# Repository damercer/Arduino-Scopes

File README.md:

# Arduino firmware for Universal-ALICE
With the goal of "Instrumentation for Every Student" in mind this project is intended to lower all barriers to providing a hardware and software platform for teaching electronic circuits to engineering students. Every student should have access to affordable hardware and software to measure their experiments.
This project offers a free open source software user interface that is compatible with hardware produced in large quantities at low cost (ranging from $5 to $20) from multiple suppliers.
#
Currently available hardware interfaces (some are works in progress):

* Arduino compatible microcontroler boards:
  + Adafruit QT Pi - SAMD21
  + Adafruit Trinket M0 (ATSAMD21)
  + Adafruit ItsyBitsy M0 Express (ATSAMD21)
  + Adafruit ItsyBitsy M4 Express (ATSAMD51)
  + Raspberry Pi Pico RP-2040
    - With external R/2R DAC or SPI DAC or PWM analog AWG output
  + SparkFun SAMD21 Mini Breakout (DEV-13664)
  + SparkFun Thing Plus - SAMD51 (DEV-14713)
  + Seeed Studio XIAO SAMD21
  + Seeed Studio XIAO RP-2040
    - With external SPI DAC or PWM analog AWG output

If you are not a technical individual or highly familiar with computer operating systems and you have your choice of computers, a Windows computer is highly recommended. You will usually run into fewer issues, if any, with that operating system.

Known Issues: If your computer encrypts files saved on external storge devices (USB disk drives) then the UF2 Bootloader method of flashing firmware to micro-controller boards will not work. You would need to use a different computer that does not encrypt files or consult your local system administrator.

Linux Operating system: On Linux computers access to USB based serial comms devices is not allowed for non root users by default. A udev rules file needs to be added. Place the 99-arduino.rules from this repository in etc/udev/rules.d

It contains one line per board / vendor:

SUBSYSTEMS=="usb", ATTRS{idVendor}=="802F", ATTRS{idProduct}=="2886", GROUP="dialout", MODE="0666"

The above idVendor value is board / vendor specific and may need to be adjusted to match your specific board(s). The one above is specifically for the XIAO SAMD21 board.

If this rules file does not work on your version of Linux there may be other things like this that work. Searching the web on how to make serial USB devices work may provide an alternate solution or consult with your local Linux expert.

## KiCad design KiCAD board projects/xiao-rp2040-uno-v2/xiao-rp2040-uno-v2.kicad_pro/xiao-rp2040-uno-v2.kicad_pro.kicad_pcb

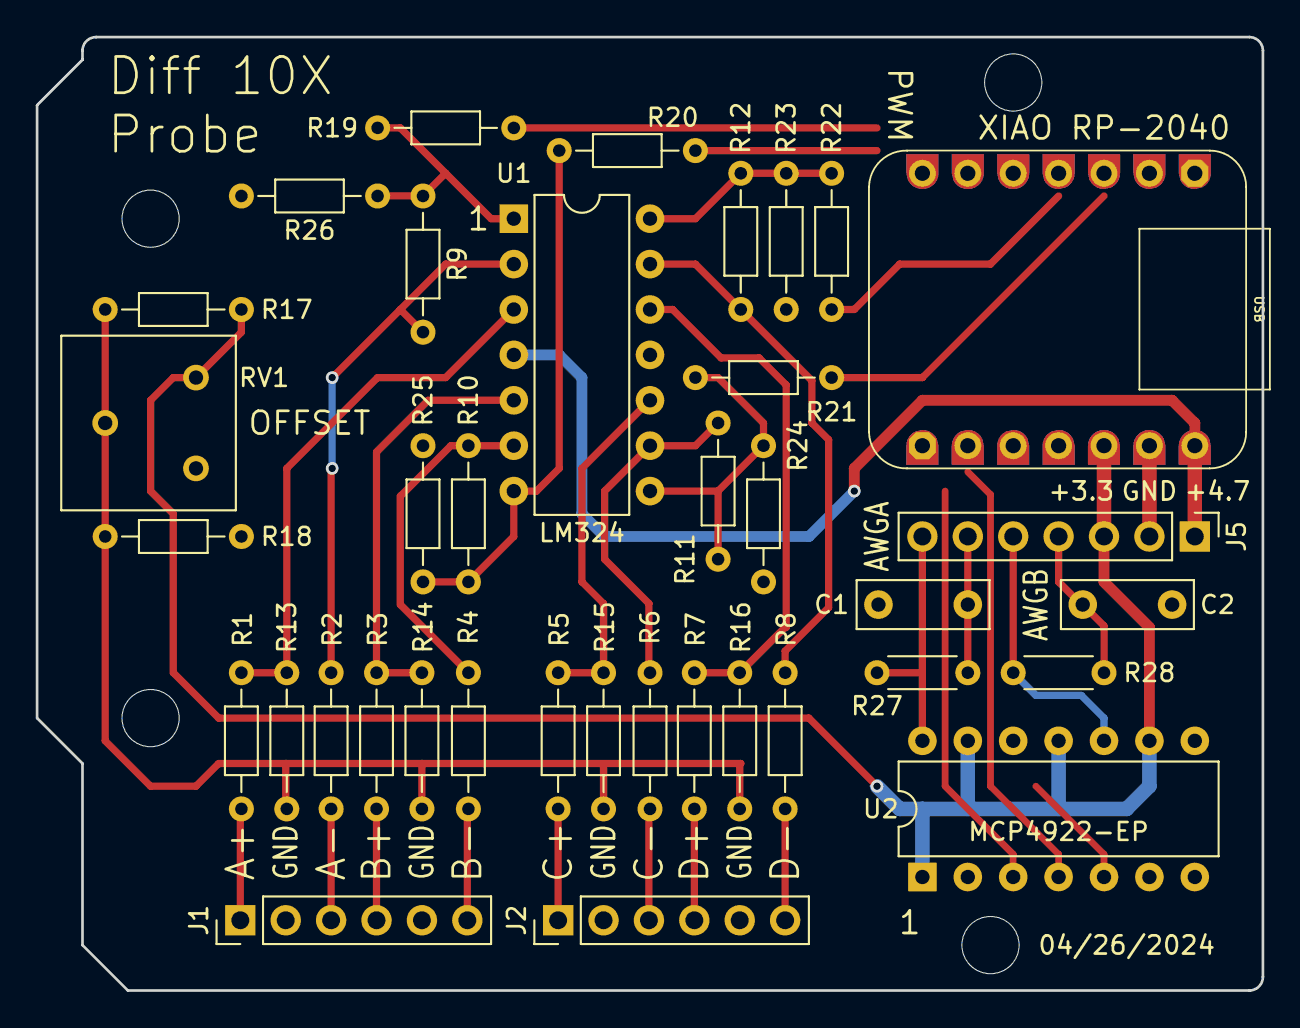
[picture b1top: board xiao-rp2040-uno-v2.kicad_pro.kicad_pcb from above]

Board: 6 copper layers, 68.6 x 53.3 mm, 42 parts (0 on the bottom side), 35 nets.

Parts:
C1, C2: C; C_Rect_L7.2mm_W2.5mm_P5.00mm_FKS2_FKP2_MKS2_MKP2
J1, J2: Conn_01x06_Pin; PinHeader_1x06_P2.54mm_Vertical
J2#2, J4: DNP; H7-HALF-HOLE-2.54
J5: Conn_01x07_Pin; PinHeader_1x07_P2.54mm_Vertical
MH1, MH2, MH3, MH4: MountingHole_3.2mm
R1, R2, R3, R4, R5, R6, R7, R8: 1Meg; R_Axial_DIN0204_L3.6mm_D1.6mm_P7.62mm_Horizontal
R9, R10, R11, R12, R13, R14, R15, R16: 100k; R_Axial_DIN0204_L3.6mm_D1.6mm_P7.62mm_Horizontal
R17, R18: 100; R_Axial_DIN0204_L3.6mm_D1.6mm_P7.62mm_Horizontal
R19, R20, R21, R22: 220; R_Axial_DIN0204_L3.6mm_D1.6mm_P7.62mm_Horizontal
R23, R24, R25, R26: 510; R_Axial_DIN0204_L3.6mm_D1.6mm_P7.62mm_Horizontal
R27, R28: 1k; R_Axial_DIN0204_L3.6mm_D1.6mm_P5.08mm_Horizontal
RV1: 500; Potentiometer_Bourns_3386F_Vertical
U1: LM324; DIP-14_W7.62mm
U2: MCP4922-EP; DIP-14_W7.62mm

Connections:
3V3: J4.5, J5.3, R17.1, RV1.1, U2.1 (VDD), U2.9 (~SHDN), U2.11 (VrefB), U2.13 (VrefA)
A0: J2#2.1, R19.1
A1: J2#2.2, R20.1
A2: J2#2.3, R21.1
A3: J2#2.4, R22.1
GND: C1.2, C2.2, J1.2, J1.5, J2.2, J2.5, J4.6, J5.2, R18.2, R23.2, R24.2, R25.2, R26.2, RV1.3, U1.11 (V-), U2.8 (~LDAC), U2.12 (AVSS)
MOSI: J4.4, U2.5 (SDI)
unnamed: J1.1, R1.2
unnamed: J1.3, R2.2
unnamed: J1.4, R3.2
unnamed: J1.6, R4.2
unnamed: J2.1, R5.2
unnamed: J2.3, R6.2
unnamed: J2.4, R7.2
unnamed: J2.6, R8.2
unnamed: C2.1, J5.4, R28.1
unnamed: J5.5, R28.2, U2.10 (VoutB)
unnamed: C1.1, J5.6, R27.1
unnamed: J5.7, R27.2, U2.14 (VoutA)
unnamed: R10.1, R20.2, R25.1, U1.7
unnamed: R11.1, R21.2, R24.1, U1.8
unnamed: R12.1, R22.2, R23.1, U1.14
unnamed: R13.1, R14.1, R15.1, R16.1, R17.2, R18.1, RV1.2
unnamed: R9.1, R19.2, R26.1, U1.1
unnamed: R1.1, R13.2, U1.3 (+)
unnamed: R2.1, R9.2, U1.2 (-)
unnamed: R3.1, R14.2, U1.5 (+)
unnamed: R4.1, R10.2, U1.6 (-)
unnamed: R5.1, R15.2, U1.10 (+)
unnamed: R6.1, R11.2, U1.9 (-)
unnamed: R7.1, R16.2, U1.12 (+)
unnamed: R8.1, R12.2, U1.13 (-)
RX: J4.1, U2.3 (~CS)
SCK: J4.2, U2.4 (SCK)
VBUS: J4.7, J5.1, U1.4 (V+)

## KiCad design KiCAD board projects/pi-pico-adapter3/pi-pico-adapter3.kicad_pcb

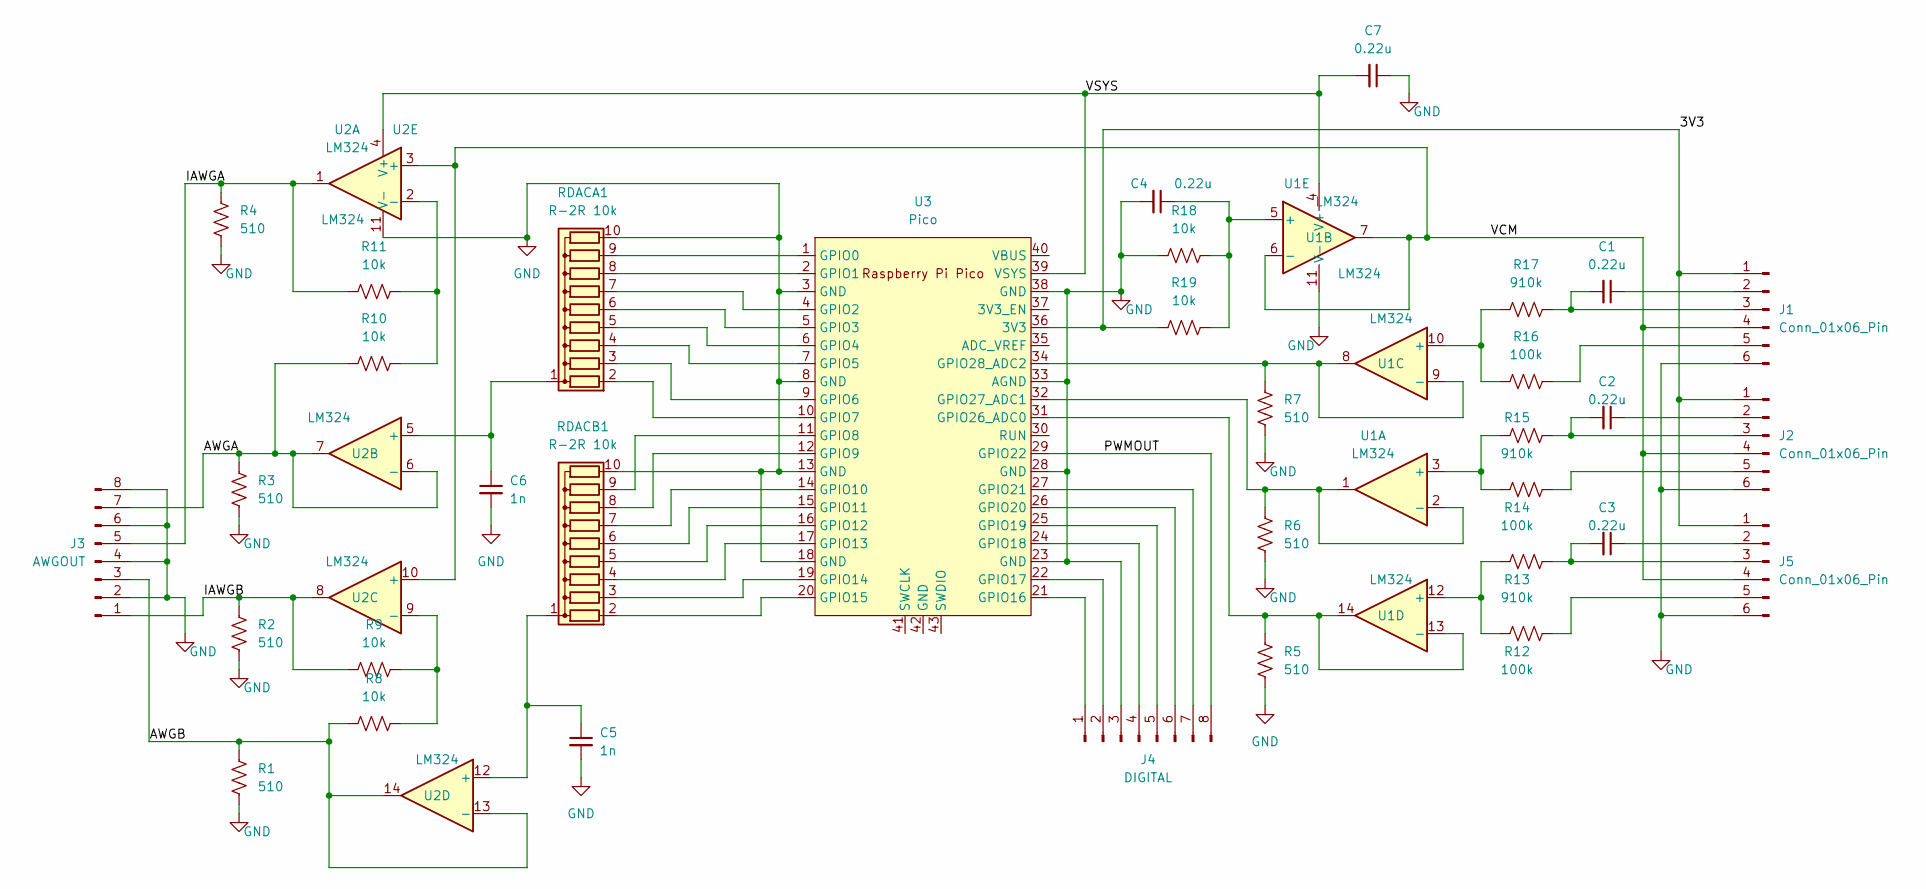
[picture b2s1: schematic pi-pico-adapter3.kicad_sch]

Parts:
C1, C2, C3, C4, C7: 0.22u; C_Rect_L7.0mm_W3.5mm_P2.50mm_P5.00mm
C5, C6: 1n; C_Rect_L7.0mm_W3.5mm_P2.50mm_P5.00mm
J1, J2, J5: Conn_01x06_Pin; PinHeader_1x06_P2.54mm_Vertical
J3: AWGOUT; PinHeader_1x08_P2.54mm_Vertical
J4: DIGITAL; PinHeader_1x08_P2.54mm_Vertical
R1, R2, R3, R4, R5, R6, R7: 510; R_Axial_DIN0204_L3.6mm_D1.6mm_P7.62mm_Horizontal
R8, R9, R10, R11, R18, R19: 10k; R_Axial_DIN0204_L3.6mm_D1.6mm_P7.62mm_Horizontal
R12, R14, R16: 100k; R_Axial_DIN0204_L3.6mm_D1.6mm_P7.62mm_Horizontal
R13, R15, R17: 910k; R_Axial_DIN0204_L3.6mm_D1.6mm_P7.62mm_Horizontal
RDACA1: R-2R 10k; R_Array_SIP10
RDACB1: R-2R 10k; R_Array_SIP10
U1, U2: LM324; DIP-14_W7.62mm
U3: Pico; RPi_Pico_SMD_TH

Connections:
/3V3: J1.1, J2.1, J5.1, R19.1, U3.36 (3V3)
/AWGA: J3.7, R3.1, R10.1, U2.6 (-), U2.7
/AWGB: J3.3, R1.1, R8.1, U2.13 (-), U2.14
/IAWGA: J3.5, R4.1, R11.1, U2.1
/IAWGB: J3.1, R2.1, R9.1, U2.8
/PWMOUT: J4.8, U3.29 (GPIO22)
/VCM: J1.4, J2.4, J5.4, U1.6 (-), U1.7, U2.3 (+), U2.10 (+)
/VSYS: C7.2, U1.4 (V+), U2.4 (V+), U3.39 (VSYS)
GND: C4.2, C5.2, C6.2, C7.1, J1.6, J2.6, J3.2, J3.4, J3.6, J3.8, J4.3, J5.6, R1.2, R2.2, R3.2, R4.2, R5.2, R6.2, R7.2, R18.1, RDACA1.10 (R9), RDACB1.10 (R9), U1.11 (V-), U2.11 (V-), U3.3 (GND), U3.8 (GND), U3.13 (GND), U3.18 (GND), U3.23 (GND), U3.28 (GND), U3.33 (AGND), U3.38 (GND)
unnamed: C1.1, J1.2
unnamed: C1.2, J1.3, R17.2
unnamed: J1.5, R16.2
unnamed: C2.1, J2.2
unnamed: C2.2, J2.3, R15.2
unnamed: J2.5, R14.2
unnamed: J4.1, U3.21 (GPIO16)
unnamed: J4.2, U3.22 (GPIO17)
unnamed: J4.4, U3.24 (GPIO18)
unnamed: J4.5, U3.25 (GPIO19)
unnamed: J4.6, U3.26 (GPIO20)
unnamed: J4.7, U3.27 (GPIO21)
unnamed: C3.1, J5.2
unnamed: C3.2, J5.3, R13.2
unnamed: J5.5, R12.2
unnamed: RDACA1.2 (R1), U3.10 (GPIO7)
unnamed: RDACA1.3 (R2), U3.9 (GPIO6)
unnamed: RDACA1.4 (R3), U3.7 (GPIO5)
unnamed: RDACA1.5 (R4), U3.6 (GPIO4)
unnamed: RDACA1.6 (R5), U3.5 (GPIO3)
unnamed: RDACA1.7 (R6), U3.4 (GPIO2)
unnamed: RDACA1.8 (R7), U3.2 (GPIO1)
unnamed: RDACA1.9 (R8), U3.1 (GPIO0)
unnamed: C6.1, RDACA1.1 (common), U2.5 (+)
unnamed: RDACB1.2 (R1), U3.20 (GPIO15)
unnamed: RDACB1.3 (R2), U3.19 (GPIO14)
unnamed: RDACB1.4 (R3), U3.17 (GPIO13)
unnamed: RDACB1.5 (R4), U3.16 (GPIO12)
unnamed: RDACB1.6 (R5), U3.15 (GPIO11)
unnamed: RDACB1.7 (R6), U3.14 (GPIO10)
unnamed: RDACB1.8 (R7), U3.12 (GPIO9)
unnamed: RDACB1.9 (R8), U3.11 (GPIO8)
unnamed: C5.1, RDACB1.1 (common), U2.12 (+)
unnamed: R14.1, R15.1, U1.3 (+)
unnamed: R6.1, U1.1, U1.2 (-), U3.32 (GPIO27_ADC1)
unnamed: C4.1, R18.2, R19.2, U1.5 (+)
unnamed: R16.1, R17.1, U1.10 (+)
unnamed: R7.1, U1.8, U1.9 (-), U3.34 (GPIO28_ADC2)
unnamed: R12.1, R13.1, U1.12 (+)
unnamed: R5.1, U1.13 (-), U1.14, U3.31 (GPIO26_ADC0)
unnamed: R10.2, R11.2, U2.2 (-)
unnamed: R8.2, R9.2, U2.9 (-)

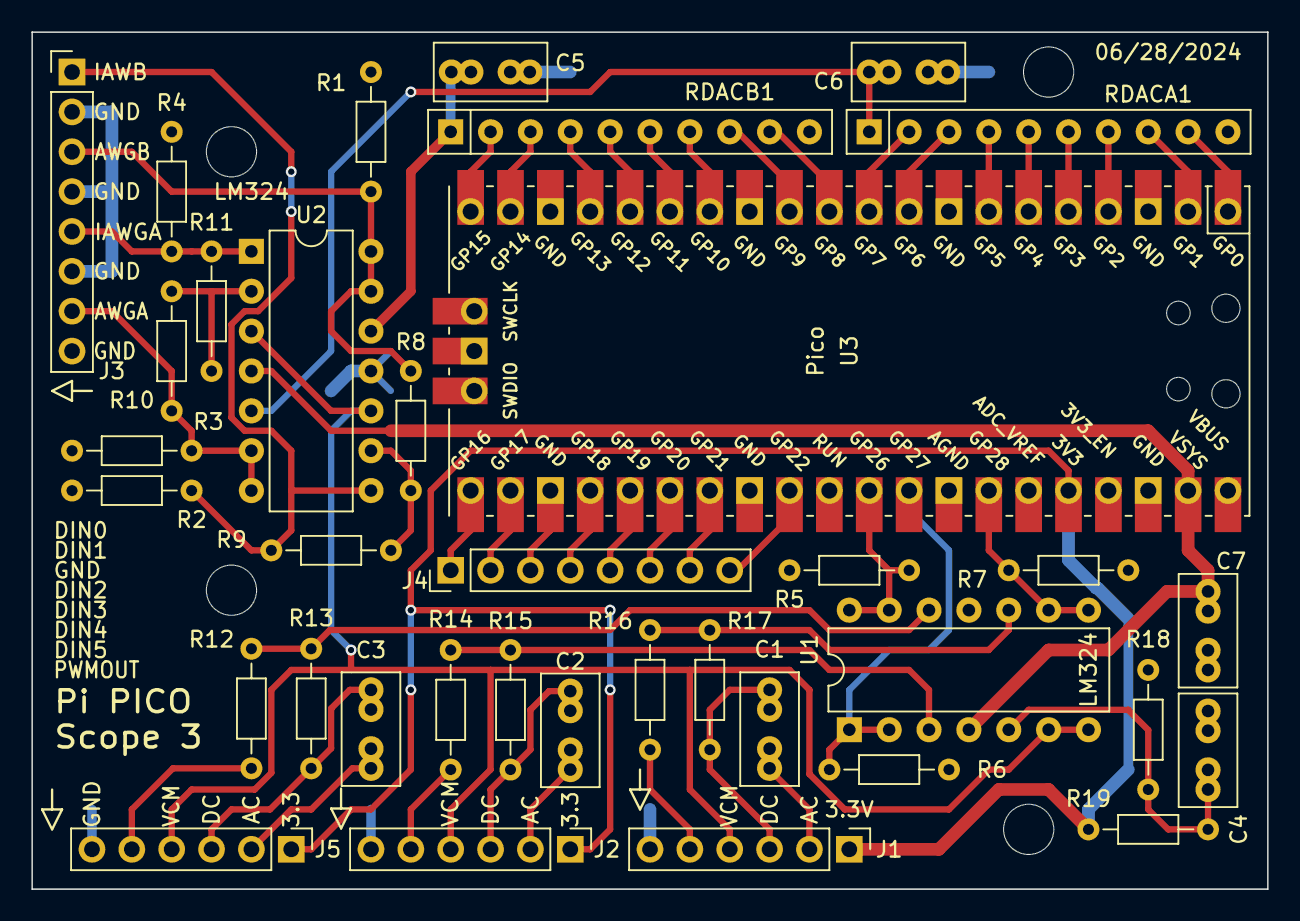
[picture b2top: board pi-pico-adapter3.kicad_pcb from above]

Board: 2 copper layers, 78.7 x 54.6 mm, 40 parts (0 on the bottom side), 51 nets.

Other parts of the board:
MH1, MH2, MH3, MH4: MountingHole_3.2mm

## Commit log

2023-10-09 First upload of source files for XIAO scope
    First up load of all the source material for the XIAO arduino scope interface for use with Universal ALICE.
2023-10-17 Oct 17 update
    Weekly up-date.
2023-10-22 Weekly update for Oct 22
    Weekly update for Oct 22
2023-10-23 New Scope hardware docs
    Added details to hardware docs for installing soltware
2023-10-31 Add Arduino How to install
    Adding files on how to set up Arduino for compiling XIAO SAMD21 code.
2023-11-03 Firmware upload
    Added up loadable precompiled firmware file and steps to put board in to bootloader.
2023-11-05 Some new updated Doc files
    These are some new updated corrected document files.
2023-12-22 Weekly Update 12/22/2023
    Weekly update for 12/22/2023.
    New faster sample rates for SAMD21 based boards.
2023-12-29 Weekly Update 29 Dec 2023
    Weekly update for Dec 29 2023. New source and .uf2 files for SAMD21 based boards. Add more hardware board options to Hardware list.
2024-01-02 First update of 2024
    Latest roll-up changes to source code and binaries. New documentations updates.
2024-01-04 Add Linux udev rules file
    Add Linux udev rules file to access USB boards
2024-01-13 Weekly Update for Jan 13 2024
    New faster PWM AWG output channels for SAMD21 based boards
    Add two SparkFun boards.
2024-01-21 Weekly Update for 1/21/2024
    This is the weekly update for 1/21/2024.
    Changes are mainly to extend the waveform capture buffer lengths to the max variable length available in the hardware.
2024-02-20 Weekly Update for 20 Feb 2024
    This is the weekly roll up of changes and fixes for 20 Feb 2024.
2024-03-02 Weekly Update for March 2 2024
    This is the weekly update for 2 March 2024. Includes extending XIAO SAMD21 to four channels.
2024-03-16 Weekly Up Date to Arduino code for certain hardware.
    Weekly update to XIAO, Qt Py and M4 Express hardware to speed up 4 channel input support and to add AWG DAC output look back through analog input Mux.
2024-03-20 Update XIAO_Scope_files.zip
    Quick update to the zip archive of all the files needed for XIAO SAMD21
2024-04-15 Update XIAO_Scope_files.zip
    Latest versions of code for XIAO SAMD21
2024-06-28 Post ASEE first up-date
    This will be the first of the post ASEE up-dates. Now including KiCAD project boards.
2024-07-01 Second post ASEE update
    This update includes bundled zip archives for specific microcontrollers
